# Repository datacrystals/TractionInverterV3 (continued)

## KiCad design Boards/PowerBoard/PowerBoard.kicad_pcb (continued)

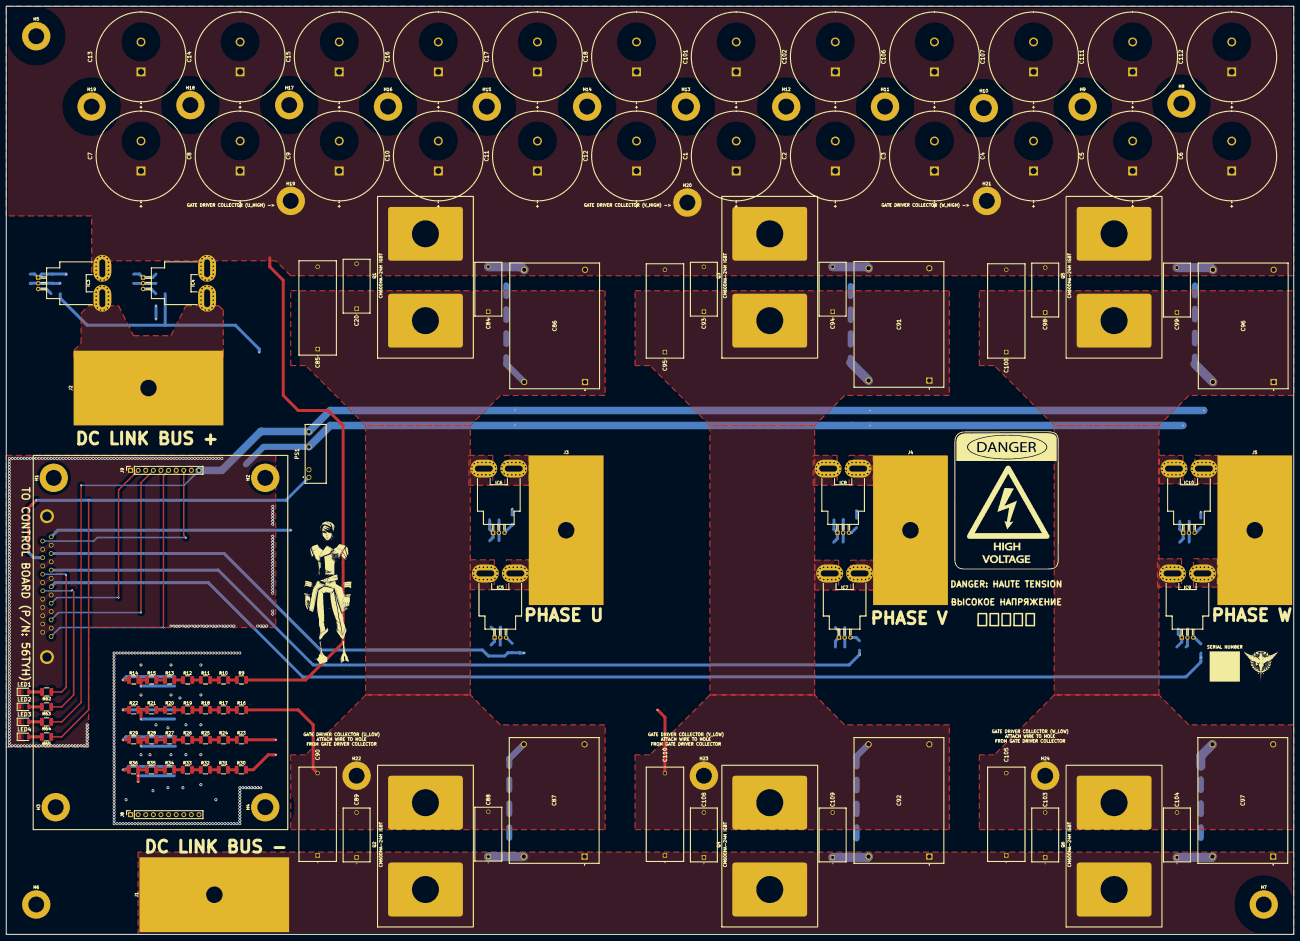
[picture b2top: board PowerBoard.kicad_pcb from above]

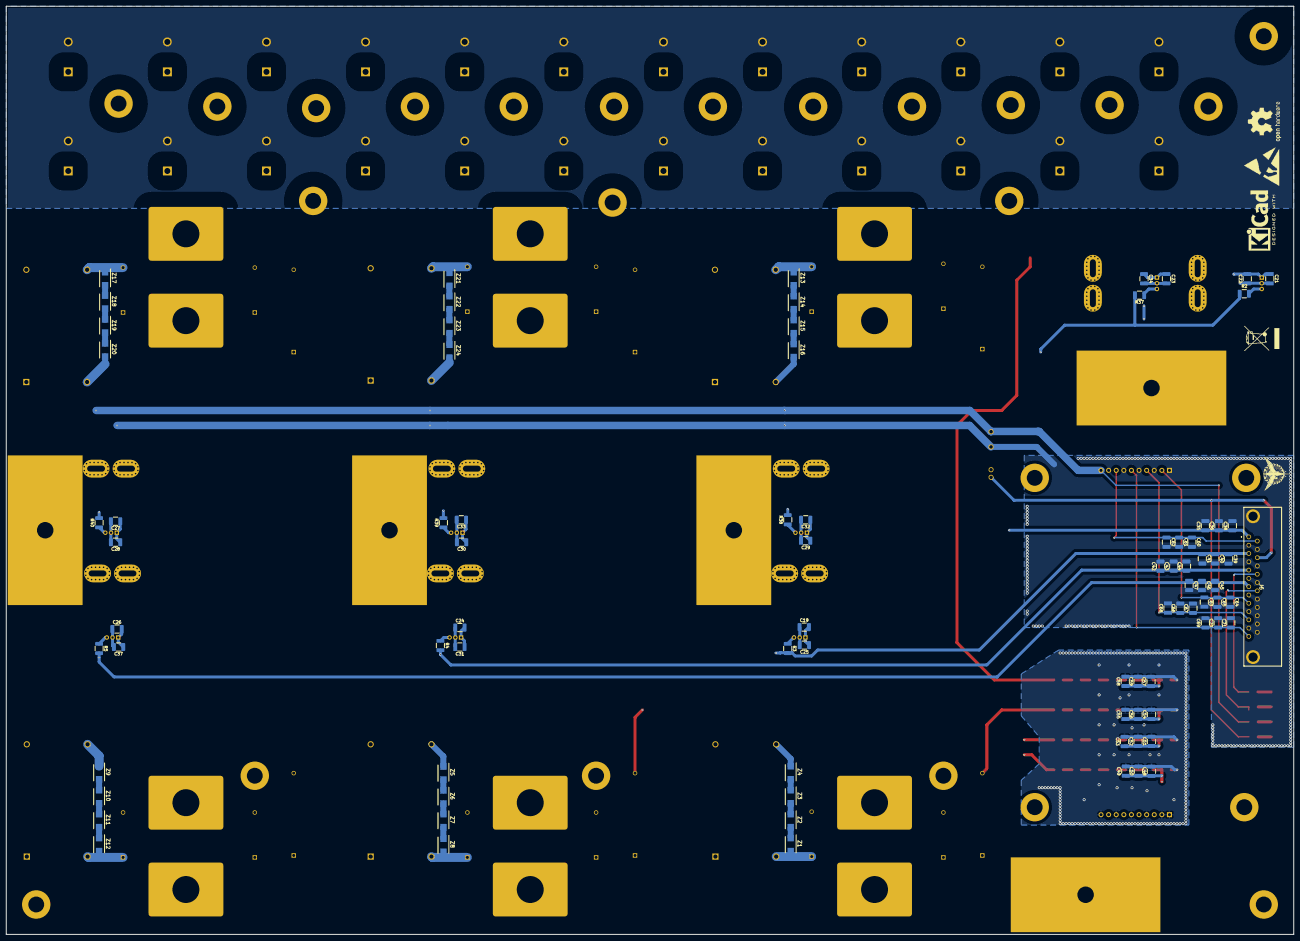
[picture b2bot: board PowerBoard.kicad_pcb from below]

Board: 4 copper layers, 430.0 x 310.0 mm, 216 parts (85 on the bottom side), 76 nets.

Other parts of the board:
H19#2, H20, H21, H22, H23, H24: MountingHole_Pad; MountingHole_5.3mm_M5_ISO7380_Pad

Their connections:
DC_LINK_BUS: H19#2.1, H20.1, H21.1; also elsewhere on the board
PHASE_U: H22.1; also elsewhere on the board
PHASE_V: H23.1; also elsewhere on the board
PHASE_W: H24.1; also elsewhere on the board

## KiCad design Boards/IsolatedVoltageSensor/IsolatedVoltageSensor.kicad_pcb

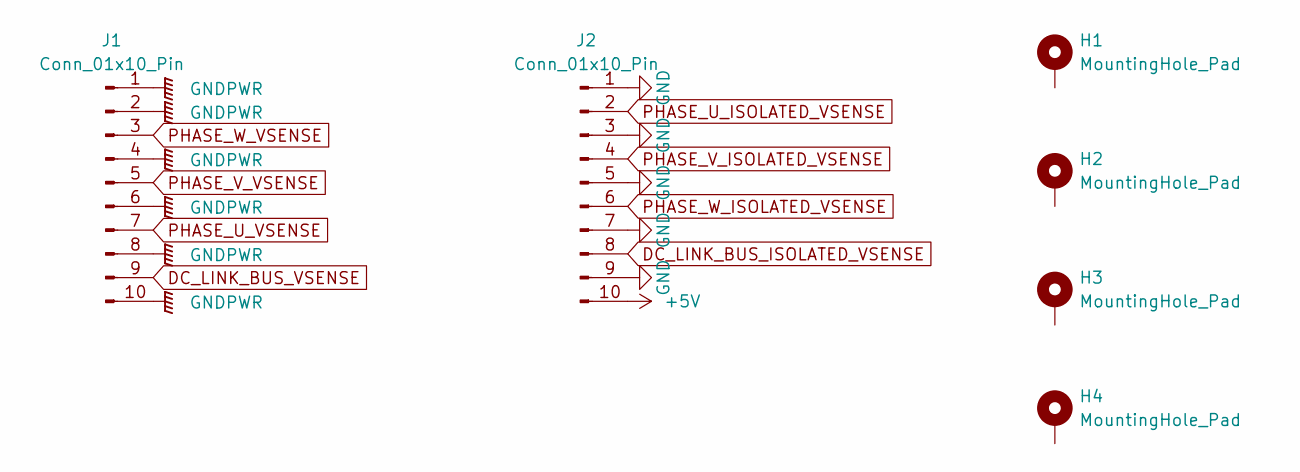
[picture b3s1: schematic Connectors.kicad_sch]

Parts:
H1, H2, H3, H4: MountingHole_Pad; MountingHole_5.3mm_M5_ISO7380_Pad
J1, J2: Conn_01x10_Pin; PinHeader_1x10_P2.54mm_Vertical

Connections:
+5V: J2.10; also elsewhere on the board
DC_LINK_BUS_ISOLATED_VSENSE: J2.8; also elsewhere on the board
DC_LINK_BUS_VSENSE: J1.9; also elsewhere on the board
GND: J2.1, J2.3, J2.5, J2.7, J2.9; also elsewhere on the board
GNDPWR: J1.1, J1.2, J1.4, J1.6, J1.8, J1.10; also elsewhere on the board
PHASE_U_ISOLATED_VSENSE: J2.2; also elsewhere on the board
PHASE_U_VSENSE: J1.7; also elsewhere on the board
PHASE_V_ISOLATED_VSENSE: J2.4; also elsewhere on the board
PHASE_V_VSENSE: J1.5; also elsewhere on the board
PHASE_W_ISOLATED_VSENSE: J2.6; also elsewhere on the board
PHASE_W_VSENSE: J1.3; also elsewhere on the board

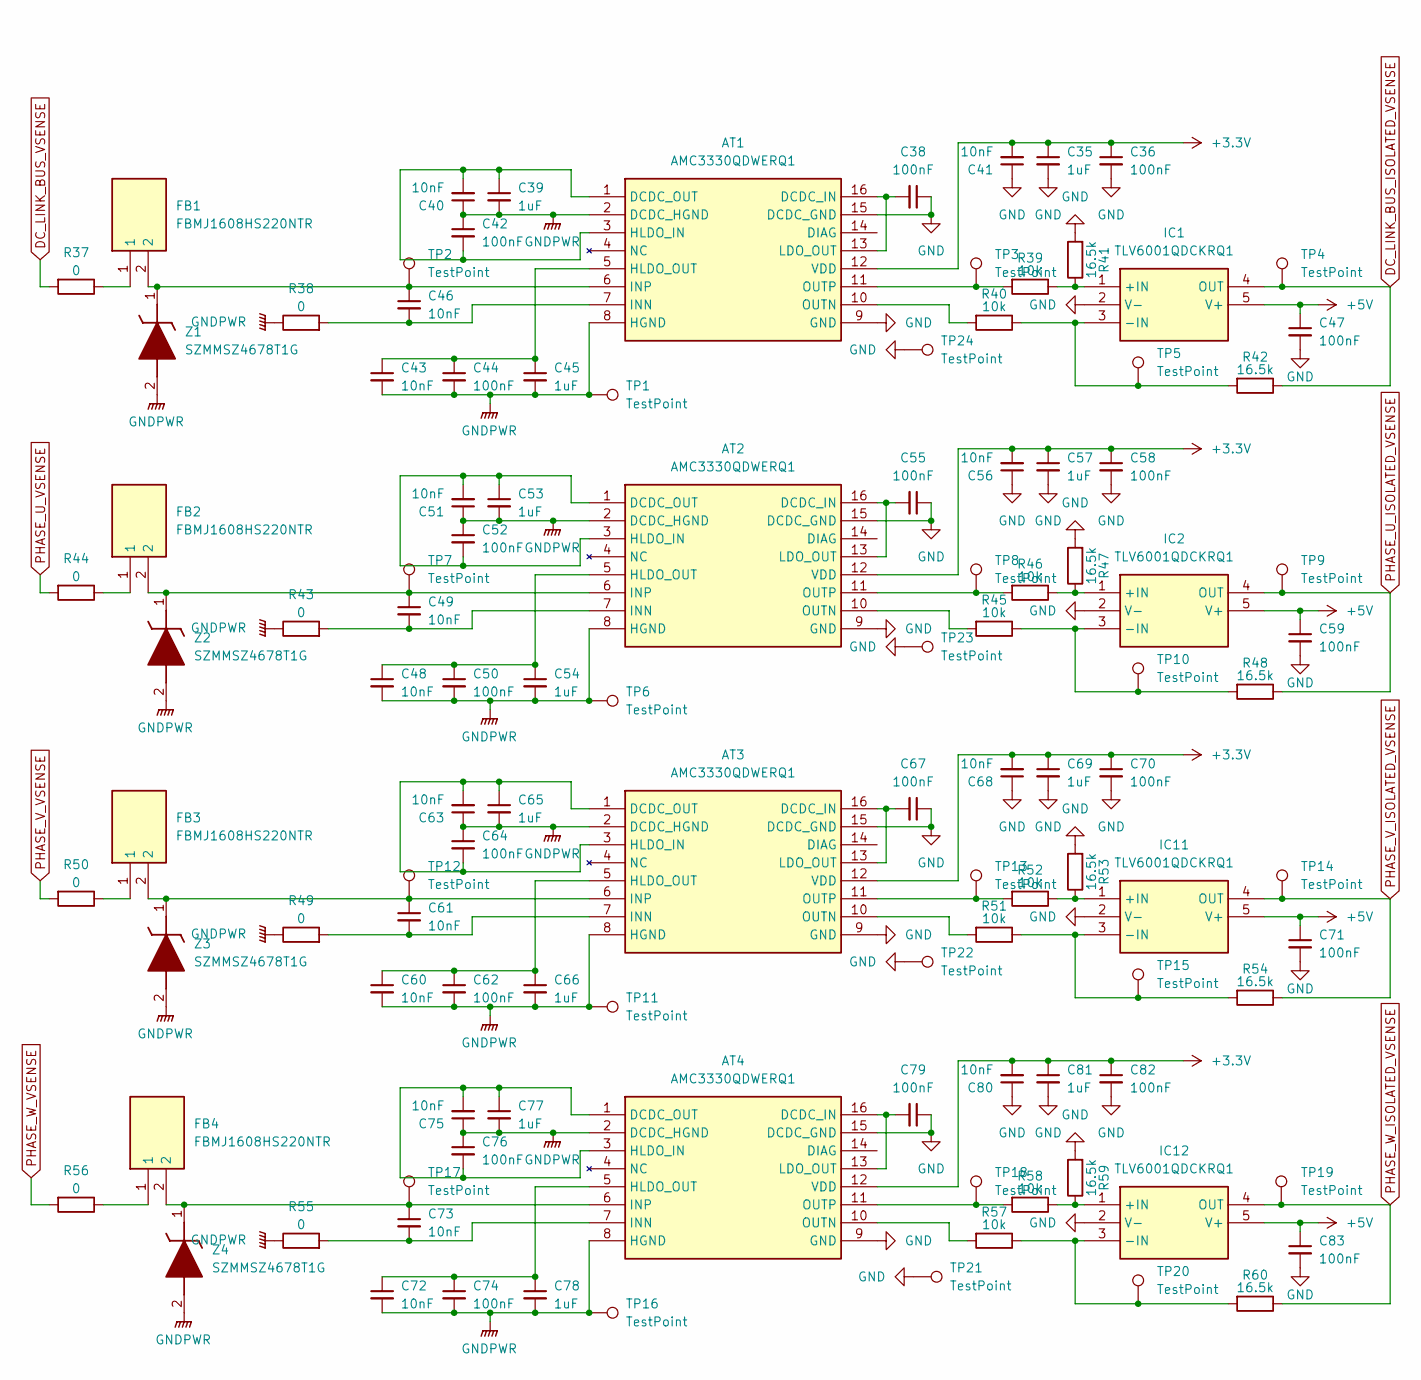
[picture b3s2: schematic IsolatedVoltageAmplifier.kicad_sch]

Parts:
AT1, AT2, AT3, AT4: AMC3330QDWERQ1; SOIC127P1030X265-16N; Mouser Part Number 595-AMC3330QDWERQ1
C35, C39, C45, C53, C54, C57, C65, C66, C69, C77, C78, C81: 1uF; C_1210_3225Metric_Pad1.33x2.70mm_HandSolder
C36, C38, C42, C44, C47, C50, C52, C55, C58, C59, C62, C64, C67, C70, C71, C74, C76, C79, C82, C83: 100nF; C_1210_3225Metric_Pad1.33x2.70mm_HandSolder
C40, C41, C43, C46, C48, C49, C51, C56, C60, C61, C63, C68, C72, C73, C75, C80: 10nF; C_1210_3225Metric_Pad1.33x2.70mm_HandSolder
FB1, FB2, FB3, FB4: FBMJ1608HS220NTR; BEADC1608X100N; Mouser Part Number 963-FBMJ1608HS220NTR
IC1, IC2, IC11, IC12: TLV6001QDCKRQ1; SOT65P210X110-5N; Mouser Part Number 595-TLV6001QDCKRQ1
R37, R38, R43, R44, R49, R50, R55, R56: 0; R_1210_3225Metric_Pad1.30x2.65mm_HandSolder
R39, R40, R45, R46, R51, R52, R57, R58: 10k; R_1210_3225Metric_Pad1.30x2.65mm_HandSolder
R41, R42, R47, R48, R53, R54, R59, R60: 16.5k; R_1210_3225Metric_Pad1.30x2.65mm_HandSolder
TP1, TP2, TP3, TP4, TP5, TP6, TP7, TP8, TP9, TP10, TP11, TP12, TP13, TP14, TP15, TP16, TP17, TP18, TP19, TP20, TP21, TP22, TP23, TP24: TestPoint; TestPoint_Loop_D2.54mm_Drill1.5mm_Beaded
Z1, Z2, Z3, Z4: SZMMSZ4678T1G; SOD3716X135N; Mouser Part Number 863-SZMMSZ4678T1G

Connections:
+3.3V: AT1.12 (VDD), AT2.12 (VDD), AT3.12 (VDD), AT4.12 (VDD), C35.1, C36.1, C41.2, C56.2, C57.1, C58.1, C68.2, C69.1, C70.1, C80.2, C81.1, C82.1; also elsewhere on the board
+5V: C47.1, C59.1, C71.1, C83.1, IC1.5 (V+), IC2.5 (V+), IC11.5 (V+), IC12.5 (V+); also elsewhere on the board
DC_LINK_BUS_ISOLATED_VSENSE: IC1.4 (OUT), R42.1, TP4.1; also elsewhere on the board
DC_LINK_BUS_VSENSE: R37.2; also elsewhere on the board
GND: AT1.9 (GND), AT1.15 (DCDC_GND), AT2.9 (GND), AT2.15 (DCDC_GND), AT3.9 (GND), AT3.15 (DCDC_GND), AT4.9 (GND), AT4.15 (DCDC_GND), C35.2, C36.2, C38.1, C41.1, C47.2, C55.1, C56.1, C57.2, C58.2, C59.2, C67.1, C68.1, C69.2, C70.2, C71.2, C79.1, C80.1, C81.2, C82.2, C83.2, IC1.2 (V-), IC2.2 (V-), IC11.2 (V-), IC12.2 (V-), R41.2, R47.2, R53.2, R59.2, TP21.1, TP22.1, TP23.1, TP24.1; also elsewhere on the board
GNDPWR: AT1.2 (DCDC_HGND), AT1.8 (HGND), AT2.2 (DCDC_HGND), AT2.8 (HGND), AT3.2 (DCDC_HGND), AT3.8 (HGND), AT4.2 (DCDC_HGND), AT4.8 (HGND), C39.2, C40.1, C42.1, C43.2, C44.2, C45.2, C48.2, C50.2, C51.1, C52.1, C53.2, C54.2, C60.2, C62.2, C63.1, C64.1, C65.2, C66.2, C72.2, C74.2, C75.1, C76.1, C77.2, C78.2, R38.1, R43.1, R49.1, R55.1, TP1.1, TP6.1, TP11.1, TP16.1, Z1.2 (A), Z2.2 (A), Z3.2 (A), Z4.2 (A); also elsewhere on the board
unnamed: AT1.13 (LDO_OUT), AT1.16 (DCDC_IN), C38.2
unnamed: AT1.1 (DCDC_OUT), AT1.3 (HLDO_IN), C39.1, C40.2, C42.2
unnamed: AT1.5 (HLDO_OUT), C43.1, C44.1, C45.1
unnamed: AT1.7 (INN), C46.2, R38.2
unnamed: AT1.6 (INP), C46.1, FB1.2, TP2.1, Z1.1 (K)
unnamed: AT1.10 (OUTN), R40.2
unnamed: AT1.11 (OUTP), R39.2, TP3.1
unnamed: AT2.13 (LDO_OUT), AT2.16 (DCDC_IN), C55.2
unnamed: AT2.1 (DCDC_OUT), AT2.3 (HLDO_IN), C51.2, C52.2, C53.1
unnamed: AT2.5 (HLDO_OUT), C48.1, C50.1, C54.1
unnamed: AT2.7 (INN), C49.2, R43.2
unnamed: AT2.6 (INP), C49.1, FB2.2, TP7.1, Z2.1 (K)
unnamed: AT2.10 (OUTN), R45.2
unnamed: AT2.11 (OUTP), R46.2, TP8.1
unnamed: AT3.13 (LDO_OUT), AT3.16 (DCDC_IN), C67.2
unnamed: AT3.1 (DCDC_OUT), AT3.3 (HLDO_IN), C63.2, C64.2, C65.1
unnamed: AT3.5 (HLDO_OUT), C60.1, C62.1, C66.1
unnamed: AT3.7 (INN), C61.2, R49.2
unnamed: AT3.6 (INP), C61.1, FB3.2, TP12.1, Z3.1 (K)
unnamed: AT3.10 (OUTN), R51.2
unnamed: AT3.11 (OUTP), R52.2, TP13.1
unnamed: AT4.13 (LDO_OUT), AT4.16 (DCDC_IN), C79.2
unnamed: AT4.1 (DCDC_OUT), AT4.3 (HLDO_IN), C75.2, C76.2, C77.1
unnamed: AT4.5 (HLDO_OUT), C72.1, C74.1, C78.1
unnamed: AT4.7 (INN), C73.2, R55.2
unnamed: AT4.6 (INP), C73.1, FB4.2, TP17.1, Z4.1 (K)
unnamed: AT4.10 (OUTN), R57.2
unnamed: AT4.11 (OUTP), R58.2, TP18.1
unnamed: FB1.1, R37.1
unnamed: FB2.1, R44.1
unnamed: FB3.1, R50.1
unnamed: FB4.1, R56.1
unnamed: IC1.1 (+IN), R39.1, R41.1
unnamed: IC1.3 (-IN), R40.1, R42.2, TP5.1
unnamed: IC2.1 (+IN), R46.1, R47.1
unnamed: IC2.3 (-IN), R45.1, R48.2, TP10.1
unnamed: IC11.1 (+IN), R52.1, R53.1
unnamed: IC11.3 (-IN), R51.1, R54.2, TP15.1
unnamed: IC12.1 (+IN), R58.1, R59.1
unnamed: IC12.3 (-IN), R57.1, R60.2, TP20.1
PHASE_U_ISOLATED_VSENSE: IC2.4 (OUT), R48.1, TP9.1; also elsewhere on the board
PHASE_U_VSENSE: R44.2; also elsewhere on the board
PHASE_V_ISOLATED_VSENSE: IC11.4 (OUT), R54.1, TP14.1; also elsewhere on the board
PHASE_V_VSENSE: R50.2; also elsewhere on the board
PHASE_W_ISOLATED_VSENSE: IC12.4 (OUT), R60.1, TP19.1; also elsewhere on the board
PHASE_W_VSENSE: R56.2; also elsewhere on the board

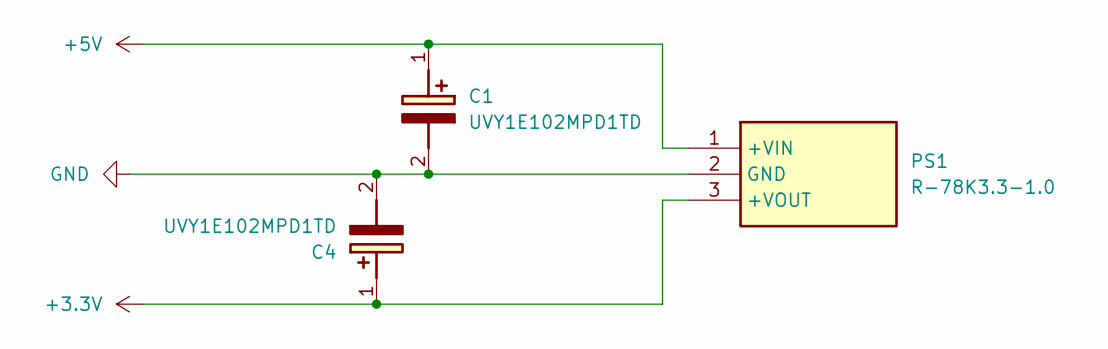
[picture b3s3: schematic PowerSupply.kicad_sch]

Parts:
C1, C4: UVY1E102MPD1TD; CAPPRD500W60D1025H1750; Mouser Part Number 647-UVY1E102MPD1TD
PS1: R-78K3.3-1.0; R78K3310; Mouser Part Number 919-R-78K3.3-1.0

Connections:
+3.3V: C4.1 (+), PS1.3 (+VOUT); also elsewhere on the board
+5V: C1.1 (+), PS1.1 (+VIN); also elsewhere on the board
GND: C1.2 (-), C4.2 (-), PS1.2 (GND); also elsewhere on the board

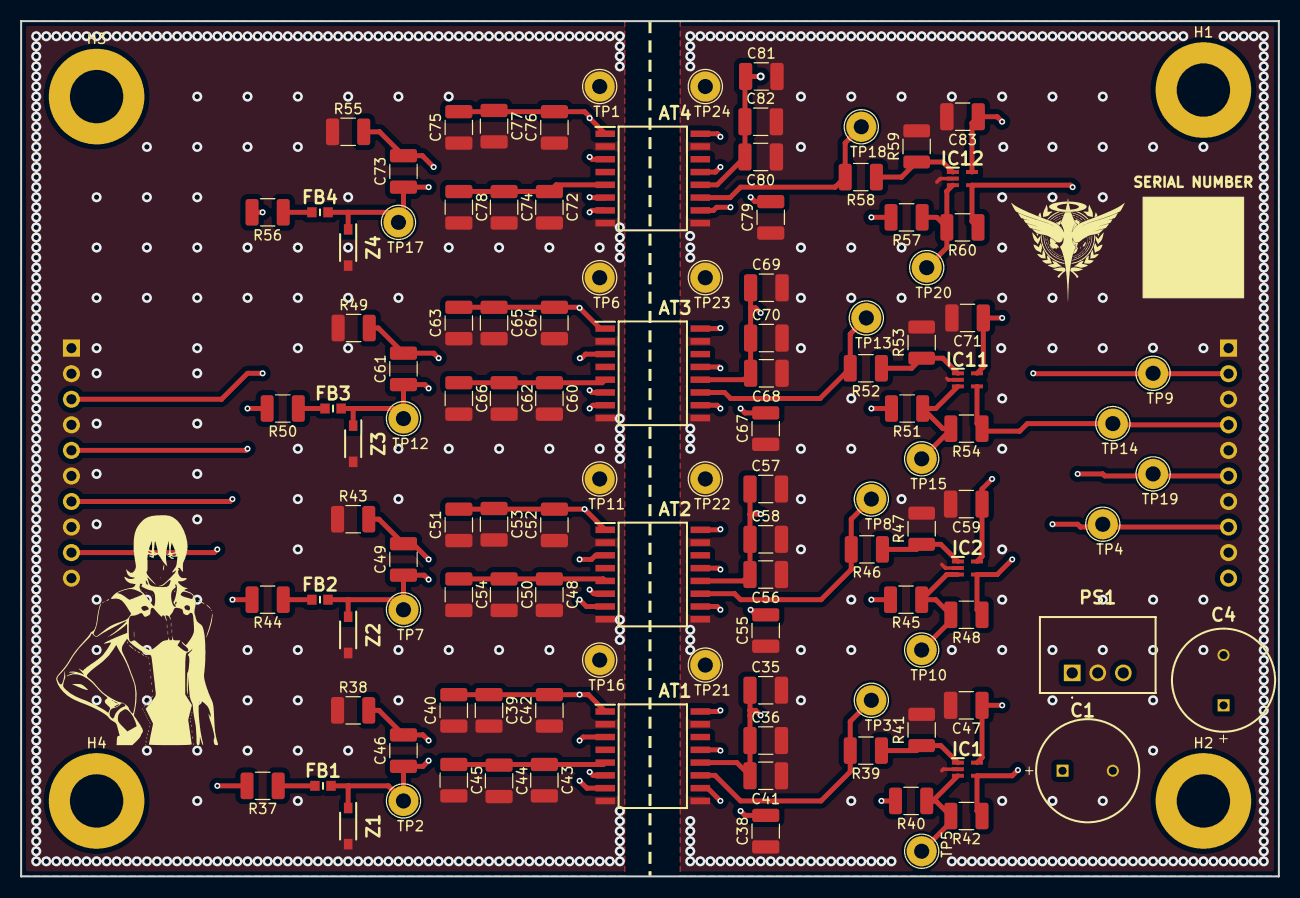
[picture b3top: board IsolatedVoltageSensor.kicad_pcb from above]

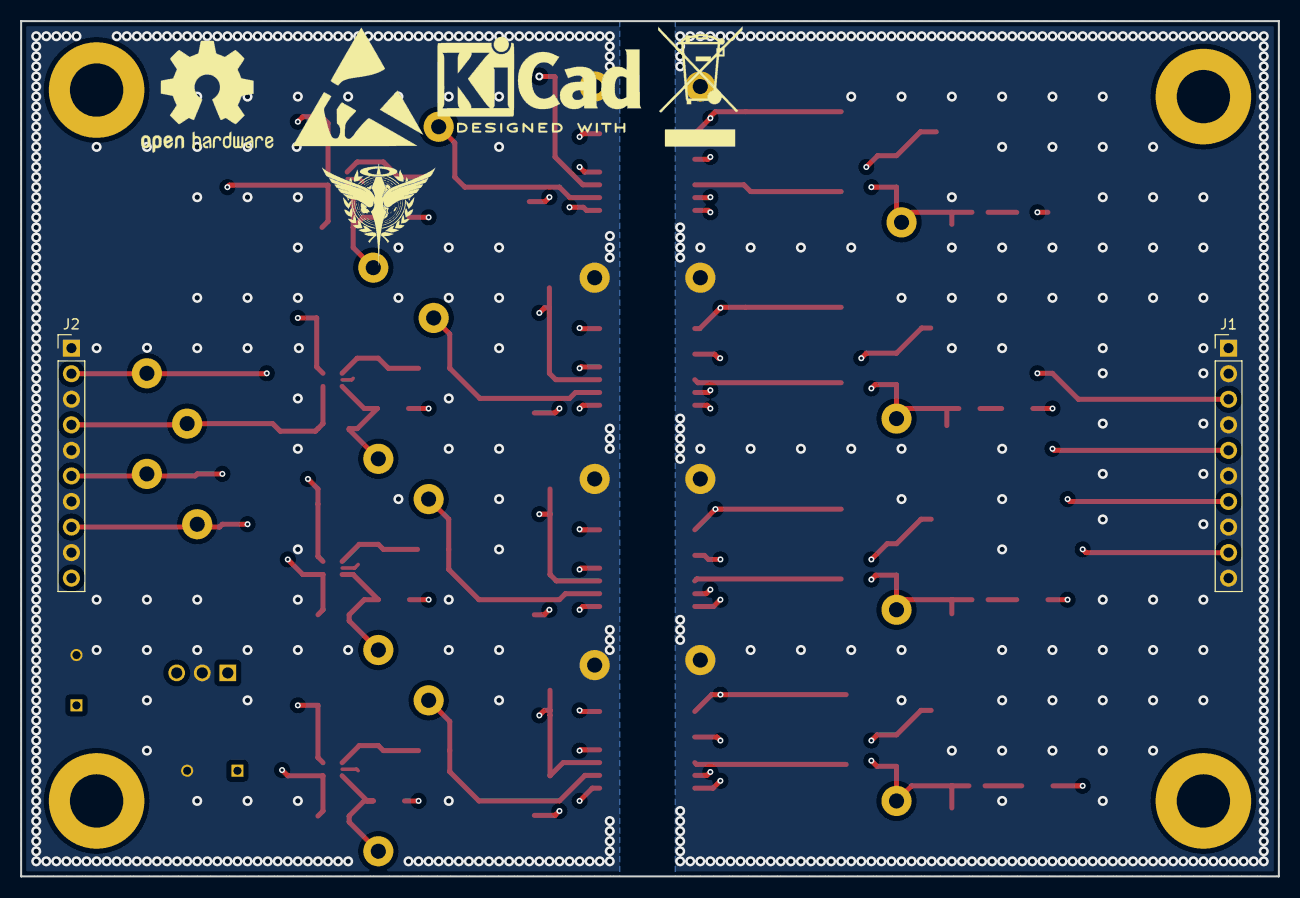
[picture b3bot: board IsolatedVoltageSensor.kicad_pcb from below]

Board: 4 copper layers, 125.0 x 85.0 mm, 121 parts (2 on the bottom side), 52 nets.

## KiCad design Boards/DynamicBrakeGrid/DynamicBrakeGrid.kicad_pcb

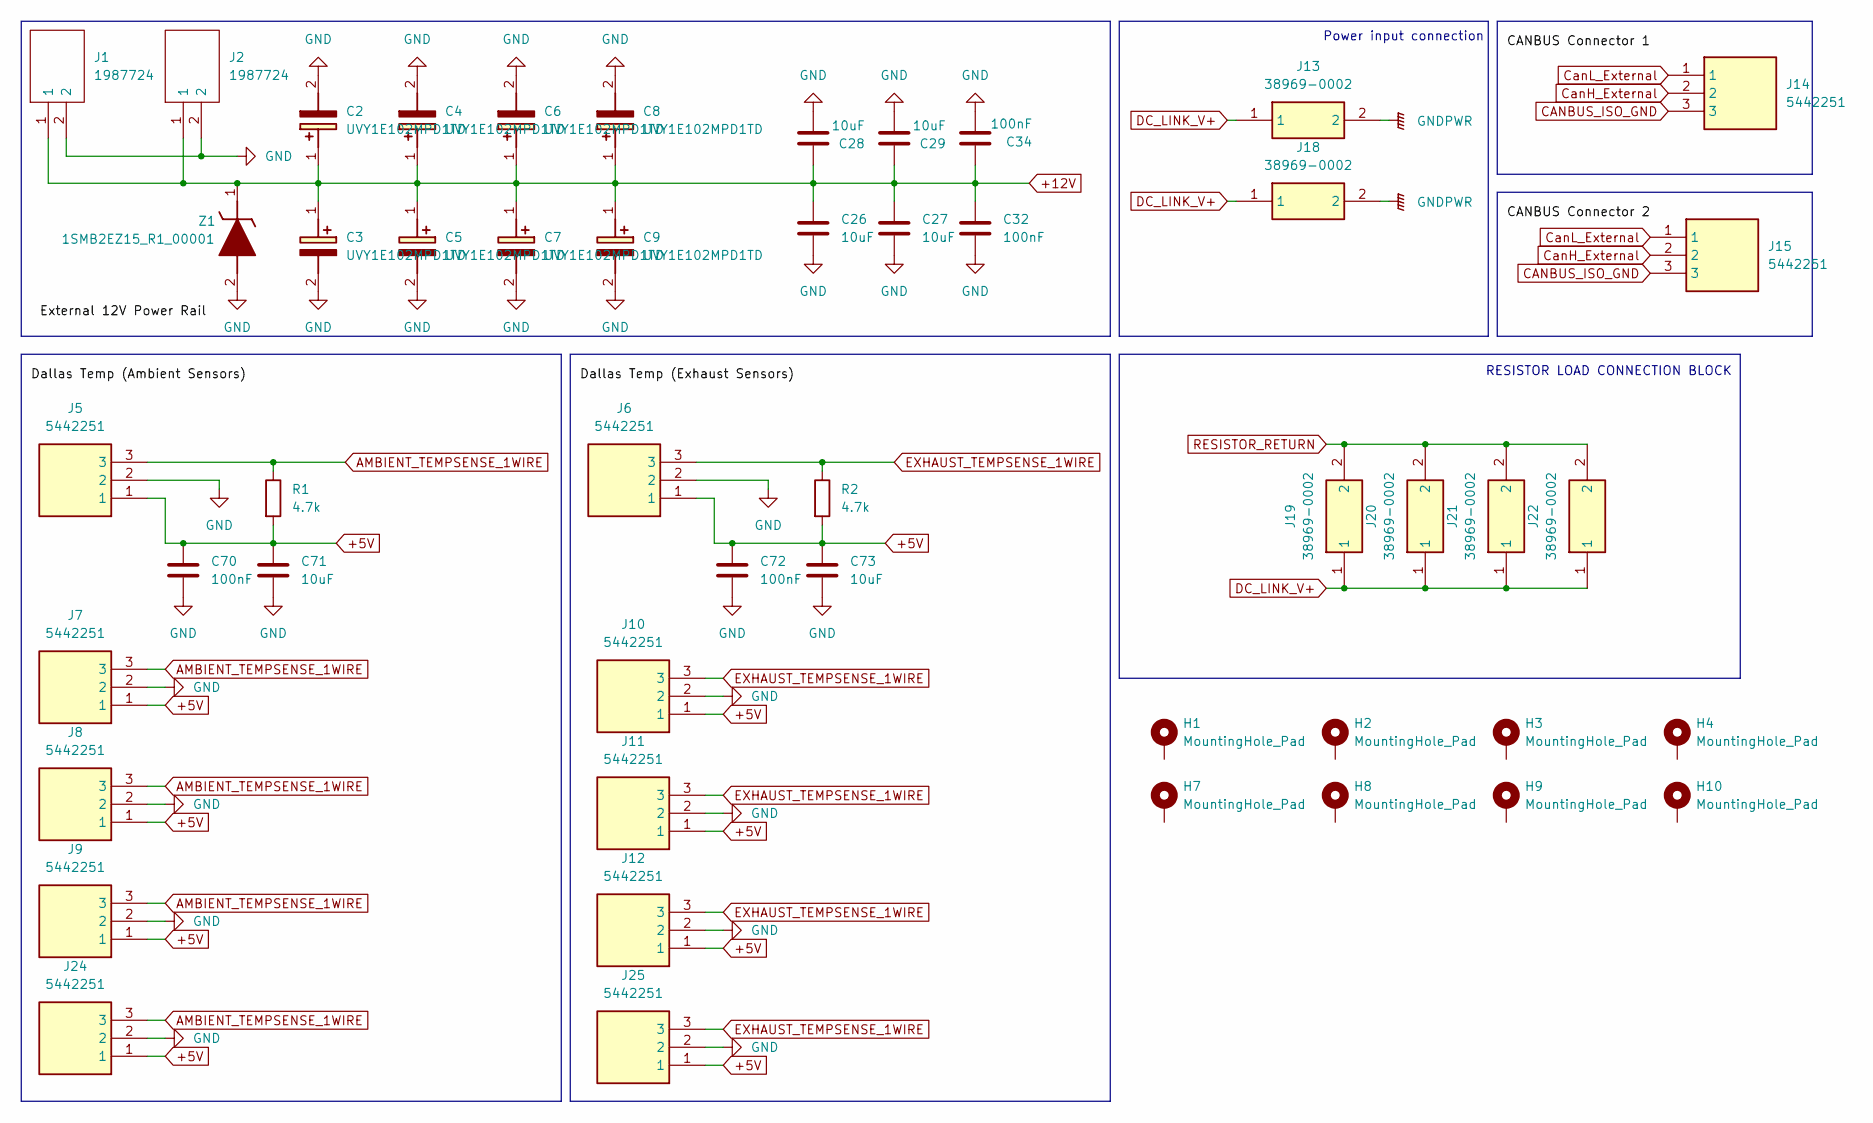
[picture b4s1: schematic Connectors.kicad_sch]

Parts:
C2, C3, C4, C5, C6, C7, C8, C9: UVY1E102MPD1TD; CAPPRD500W60D1025H1750; Mouser Part Number 647-UVY1E102MPD1TD
C26, C27, C28, C29, C71, C73: 10uF; C_1210_3225Metric_Pad1.33x2.70mm_HandSolder
C32, C34, C70, C72: 100nF; C_1210_3225Metric_Pad1.33x2.70mm_HandSolder
H1, H2, H3, H4, H7, H8, H9, H10: MountingHole_Pad; MountingHole_5.3mm_M5_ISO7380_Pad
J1, J2: 1987724; Mouser Part Number 651-1987724
J5, J6, J7, J8, J9, J10, J11, J12, J14, J15, J24, J25: 5442251; Mouser Part Number 651-5442251
J13, J18, J19, J20, J21, J22: 38969-0002; 389690002; Mouser Part Number 538-38969-0002
R1, R2: 4.7k; R_1210_3225Metric_Pad1.30x2.65mm_HandSolder
Z1: 1SMB2EZ15_R1_00001; Mouser Part Number 241-1SMB2EZ15R100001

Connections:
+5V: C70.1, C71.1, C72.1, C73.1, J5.1, J6.1, J7.1, J8.1, J9.1, J10.1, J11.1, J12.1, J24.1, J25.1, R1.2, R2.2; also elsewhere on the board
+12V: C2.1 (+), C3.1 (+), C4.1 (+), C5.1 (+), C6.1 (+), C7.1 (+), C8.1 (+), C9.1 (+), C26.1, C27.1, C28.1, C29.1, C32.1, C34.1, J1.1, J2.1, Z1.1 (K); also elsewhere on the board
AMBIENT_TEMPSENSE_1WIRE: J5.3, J7.3, J8.3, J9.3, J24.3, R1.1; also elsewhere on the board
CANBUS_ISO_GND: J14.3, J15.3; also elsewhere on the board
CanH_External: J14.2, J15.2; also elsewhere on the board
CanL_External: J14.1, J15.1; also elsewhere on the board
DC_LINK_V+: J13.1, J18.1, J19.1, J20.1, J21.1, J22.1; also elsewhere on the board
EXHAUST_TEMPSENSE_1WIRE: J6.3, J10.3, J11.3, J12.3, J25.3, R2.1; also elsewhere on the board
GND: C2.2 (-), C3.2 (-), C4.2 (-), C5.2 (-), C6.2 (-), C7.2 (-), C8.2 (-), C9.2 (-), C26.2, C27.2, C28.2, C29.2, C32.2, C34.2, C70.2, C71.2, C72.2, C73.2, J1.2, J2.2, J5.2, J6.2, J7.2, J8.2, J9.2, J10.2, J11.2, J12.2, J24.2, J25.2, Z1.2 (A); also elsewhere on the board
GNDPWR: J13.2, J18.2; also elsewhere on the board
RESISTOR_RETURN: J19.2, J20.2, J21.2, J22.2; also elsewhere on the board

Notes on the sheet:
RESISTOR LOAD CONNECTION BLOCK
Power input connection

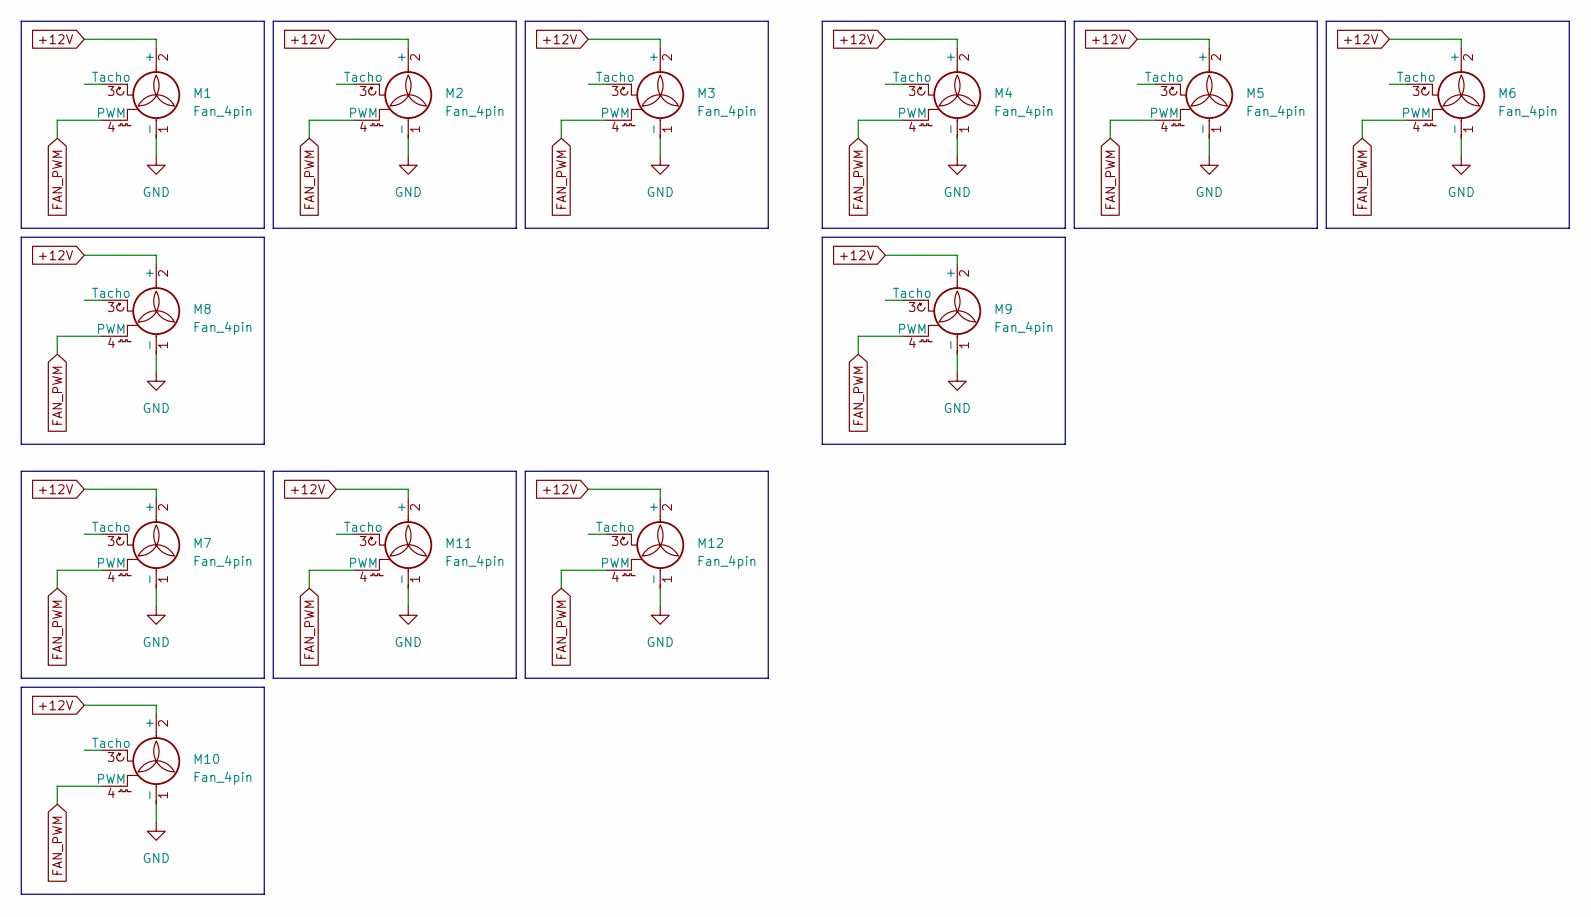
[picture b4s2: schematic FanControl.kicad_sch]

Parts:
M1, M2, M3, M4, M5, M6, M7, M8, M9, M10, M11, M12: Fan_4pin; FanPinHeader_1x04_P2.54mm_Vertical

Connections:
+12V: M1.2 (+), M2.2 (+), M3.2 (+), M4.2 (+), M5.2 (+), M6.2 (+), M7.2 (+), M8.2 (+), M9.2 (+), M10.2 (+), M11.2 (+), M12.2 (+); also elsewhere on the board
FAN_PWM: M1.4 (PWM), M2.4 (PWM), M3.4 (PWM), M4.4 (PWM), M5.4 (PWM), M6.4 (PWM), M7.4 (PWM), M8.4 (PWM), M9.4 (PWM), M10.4 (PWM), M11.4 (PWM), M12.4 (PWM); also elsewhere on the board
GND: M1.1 (-), M2.1 (-), M3.1 (-), M4.1 (-), M5.1 (-), M6.1 (-), M7.1 (-), M8.1 (-), M9.1 (-), M10.1 (-), M11.1 (-), M12.1 (-); also elsewhere on the board

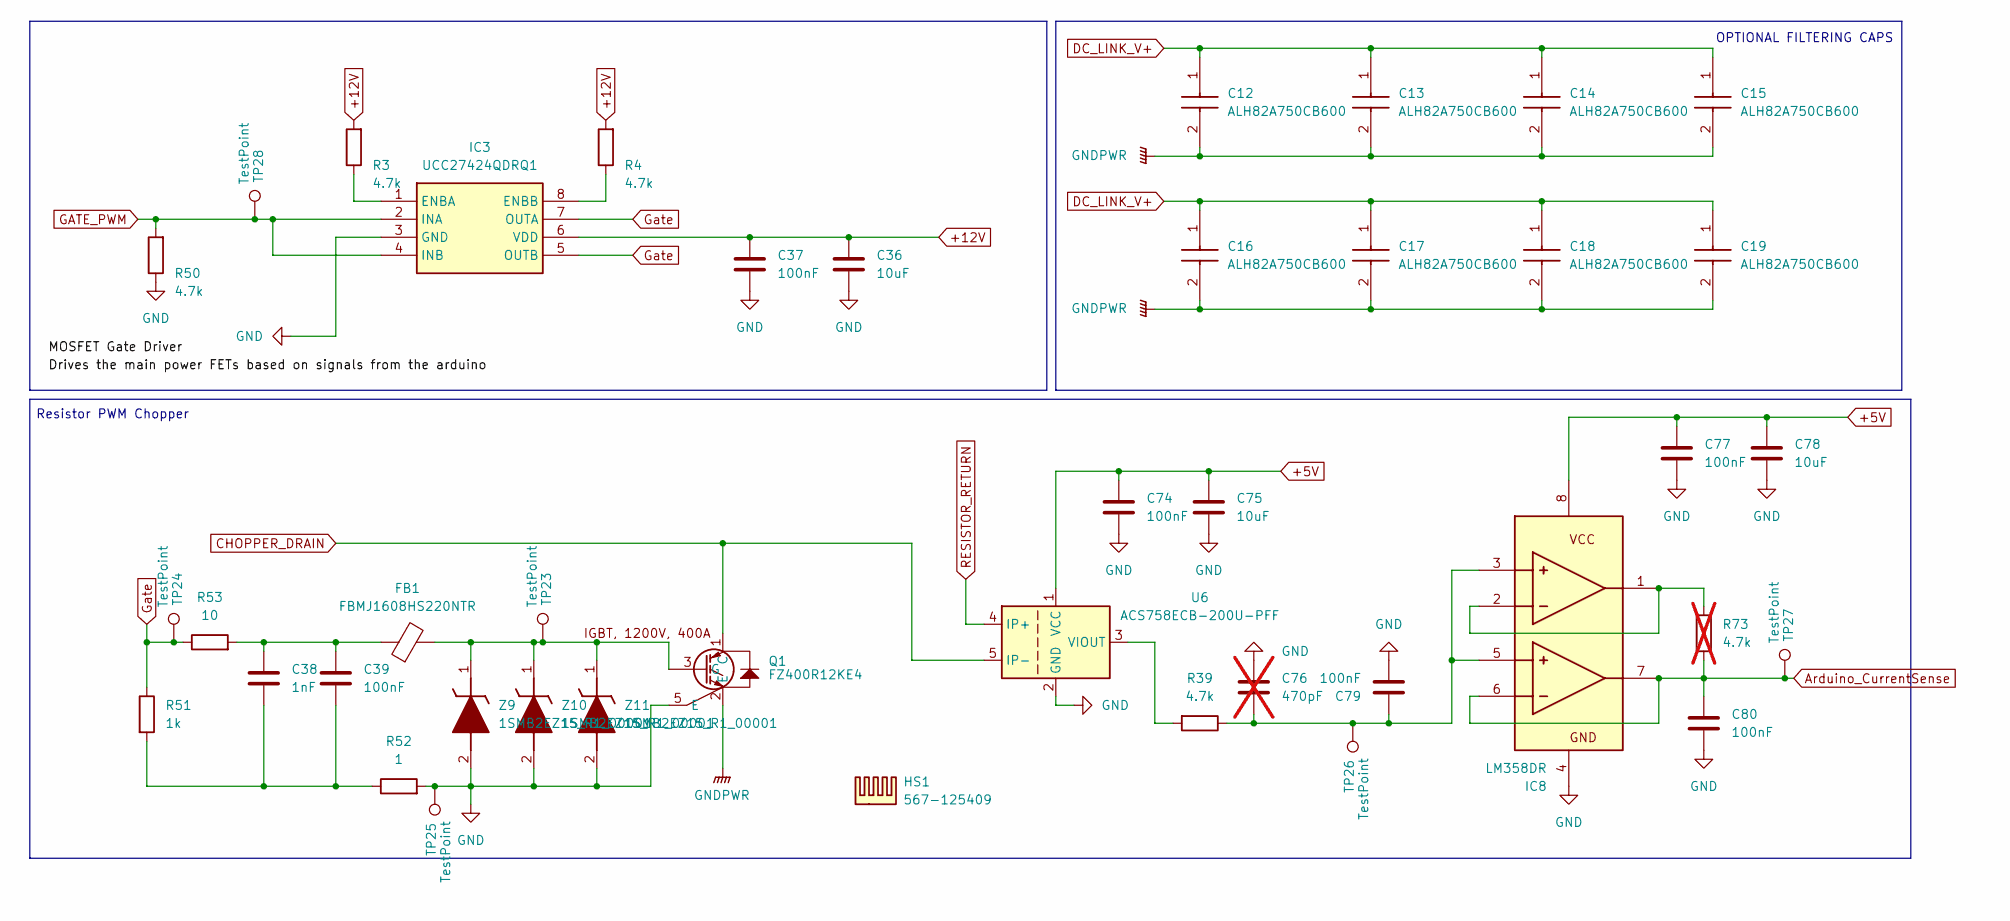
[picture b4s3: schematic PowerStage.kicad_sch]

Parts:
C12, C13, C14, C15, C16, C17, C18, C19: ALH82A750CB600; Mouser Part Number 80-ALH82A750CB600
C36, C75, C78: 10uF; C_1210_3225Metric_Pad1.33x2.70mm_HandSolder
C37, C39, C74, C77, C79, C80: 100nF; C_1210_3225Metric_Pad1.33x2.70mm_HandSolder
C38: 1nF; C_1210_3225Metric_Pad1.33x2.70mm_HandSolder
C76: 470pF; C_1210_3225Metric_Pad1.33x2.70mm_HandSolder; not fitted
FB1: FBMJ1608HS220NTR; BEADC1608X100N; Mouser Part Number 963-FBMJ1608HS220NTR
HS1: 567-125409
IC3: UCC27424QDRQ1; SOIC127P600X175-8N; Mouser Part Number 595-UCC27424QDRQ1
IC8: LM358DR; SOIC127P600X175-8N; Mouser Part Number 595-LM358DR
Q1: FZ400R12KE4
R3, R4, R39, R50: 4.7k; R_1210_3225Metric_Pad1.30x2.65mm_HandSolder
R51: 1k; R_1210_3225Metric_Pad1.30x2.65mm_HandSolder
R52: 1; R_1210_3225Metric_Pad1.30x2.65mm_HandSolder
R53: 10; R_1210_3225Metric_Pad1.30x2.65mm_HandSolder
R73: 4.7k; R_1210_3225Metric_Pad1.30x2.65mm_HandSolder; not fitted
TP23, TP24, TP25, TP26, TP27, TP28: TestPoint; TestPoint_Loop_D2.54mm_Drill1.5mm_Beaded
U6: ACS758ECB-200U-PFF; Allegro_CB_PFF
Z9, Z10, Z11: 1SMB2EZ15_R1_00001; Mouser Part Number 241-1SMB2EZ15R100001

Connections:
+5V: C74.1, C75.1, C77.1, C78.1, IC8.8 (V+), U6.1 (VCC); also elsewhere on the board
+12V: C36.1, C37.1, IC3.6 (VDD), R3.2, R4.2; also elsewhere on the board
Arduino_CurrentSense: C80.1, IC8.6 (IN2-), IC8.7 (OUT2), R73.1, TP27.1; also elsewhere on the board
CHOPPER_DRAIN: Q1.1 (C), U6.5 (IP-); also elsewhere on the board
DC_LINK_V+: C12.1, C13.1, C14.1, C15.1, C16.1, C17.1, C18.1, C19.1; also elsewhere on the board
GATE_PWM: IC3.2 (INA), IC3.4 (INB), R50.2, TP28.1; also elsewhere on the board
GND: C36.2, C37.2, C74.2, C75.2, C76.1, C77.2, C78.2, C79.2, C80.2, IC3.3 (GND), IC8.4 (V-), Q1.5 (E), R50.1, R52.2, TP25.1, U6.2 (GND), Z9.2 (A), Z10.2 (A), Z11.2 (A); also elsewhere on the board
GNDPWR: C12.2, C13.2, C14.2, C15.2, C16.2, C17.2, C18.2, C19.2, Q1.2 (E); also elsewhere on the board
Gate: IC3.5 (OUTB), IC3.7 (OUTA), R51.1, R53.1, TP24.1
unnamed: C38.1, C39.1, R51.2, R52.1
unnamed: C38.2, C39.2, FB1.1, R53.2
unnamed: IC3.1 (ENBA), R3.1
unnamed: IC3.8 (ENBB), R4.1
unnamed: C76.2, C79.1, IC8.3 (IN1+), IC8.5 (IN2+), R39.1, TP26.1
unnamed: IC8.1 (OUT1), IC8.2 (IN1-), R73.2
unnamed: FB1.2, Q1.3 (G), TP23.1, Z9.1 (K), Z10.1 (K), Z11.1 (K)
unnamed: R39.2, U6.3 (VIOUT)
RESISTOR_RETURN: U6.4 (IP+); also elsewhere on the board

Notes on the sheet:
OPTIONAL FILTERING CAPS
Resistor PWM Chopper

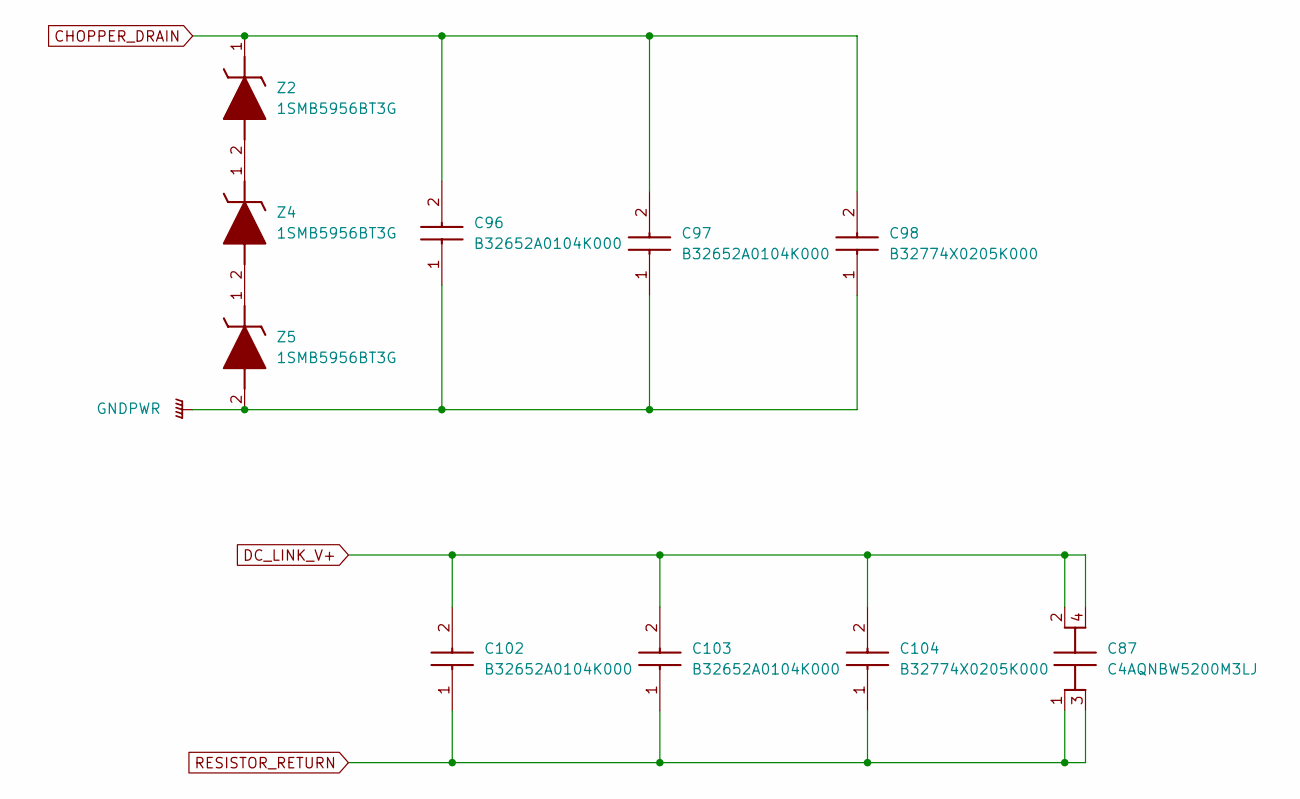
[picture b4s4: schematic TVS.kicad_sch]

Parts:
C87: C4AQNBW5200M3LJ; Mouser Part Number 80-C4AQNBW5200M3LJ
C96, C97, C102, C103: B32652A0104K000; B32652__18_x_9_; Mouser Part Number 871-B32652A104K
C98, C104: B32774X0205K000; B32774X__31.5_x_12.5_; Mouser Part Number 871-B32774X0205K000
Z2, Z4, Z5: 1SMB5956BT3G; DIOM5436X247N; Mouser Part Number 863-1SMB5956BT3G

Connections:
CHOPPER_DRAIN: C96.2, C97.2, C98.2, Z2.1 (K); also elsewhere on the board
DC_LINK_V+: C87.2, C87.4, C102.2, C103.2, C104.2; also elsewhere on the board
GNDPWR: C96.1, C97.1, C98.1, Z5.2 (A); also elsewhere on the board
unnamed: Z2.2 (A), Z4.1 (K)
unnamed: Z4.2 (A), Z5.1 (K)
RESISTOR_RETURN: C87.1, C87.3, C102.1, C103.1, C104.1; also elsewhere on the board
